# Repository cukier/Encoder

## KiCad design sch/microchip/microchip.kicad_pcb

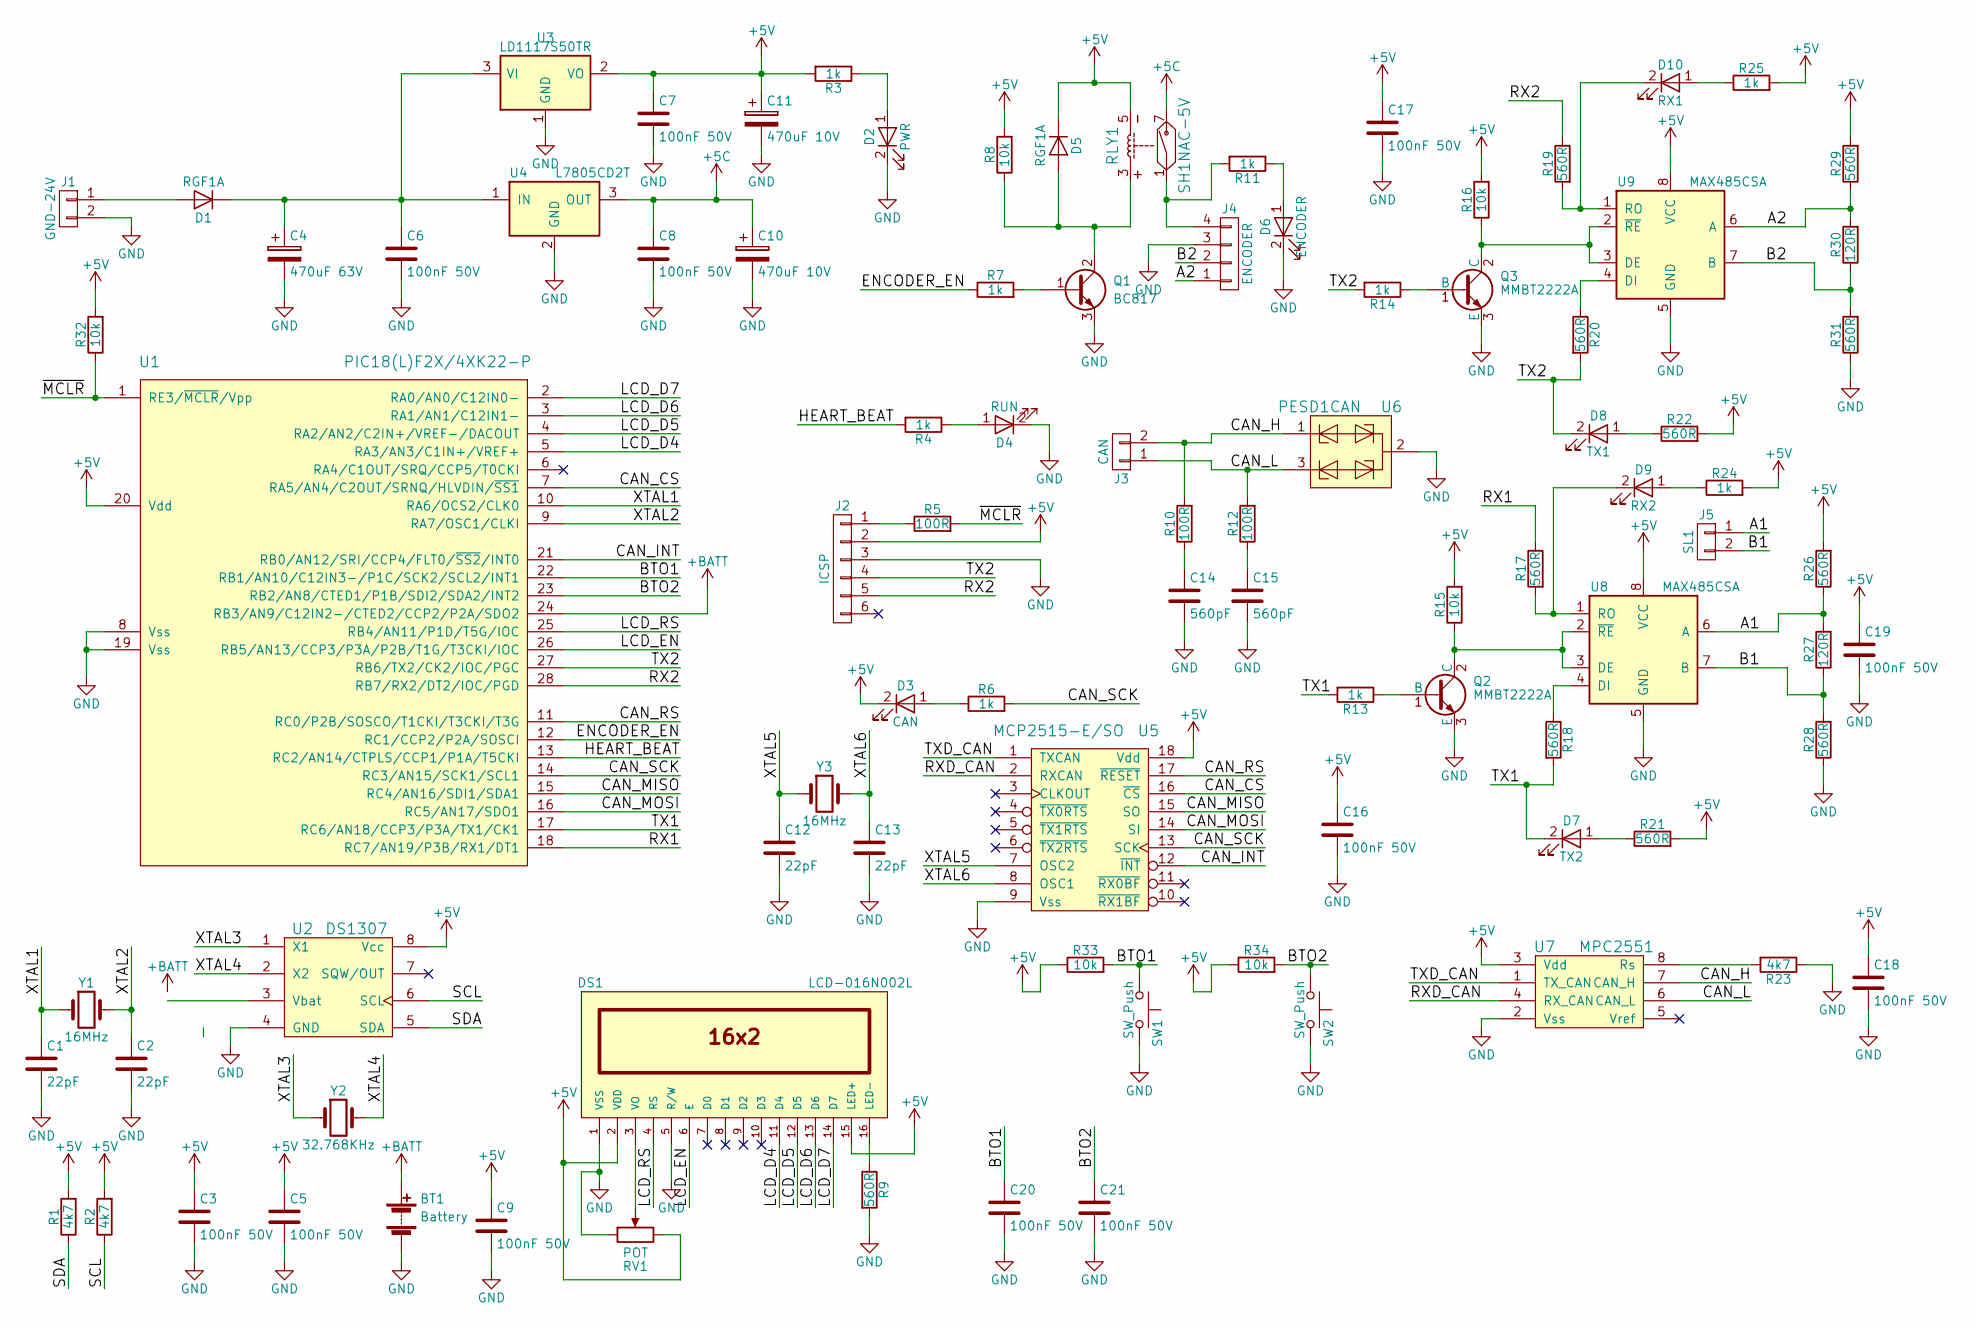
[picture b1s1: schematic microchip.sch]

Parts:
BT1: Battery; keystone_103
C1, C2, C12, C13: 22pF; c_0805
C3, C5, C6, C7, C8, C9, C16, C17, C18, C19, C20, C21: 100nF 50V; c_0805
C4: 470uF 63V; CP_12.5x25mm
C10, C11: 470uF 10V; CP_8x11.5mm
C14, C15: 560pF; c_0805
D1, D5: RGF1A; do214ac
D2: PWR; Led_0805
D3: CAN; Led_0805
D4: RUN; Led_0805
D6: ENCODER; Led_0805
D7: TX2; Led_0805
D8: TX1; Led_0805
D9: RX2; Led_0805
D10: RX1; Led_0805
DS1: LCD-016N002L; lcd_16x2
J1: GND-24V; mkds_1,5-2
J2: ICSP; pin_strip_6
J3: CAN; mkds_1,5-2
J4: ENCODER; mkds_1,5-4
J5: SL1; mkds_1,5-2
Q1: BC817; sot23
Q2, Q3: MMBT2222A; sot23
R1, R2, R23: 4k7; r_0805
R3, R4, R6, R7, R11, R13, R14, R24, R25: 1k; r_0805
R5, R10, R12: 100R; r_0805
R8, R15, R16, R32, R33, R34: 10k; r_0805
R9, R17, R18, R19, R20, R21, R22, R26, R28, R29, R31: 560R; r_0805
R27, R30: 120R; r_0805
RLY1: SH1NAC-5V; relay_9001
RV1: POT; trim_murata_pva2a
SW1, SW2: SW_Push; PCB_PUSH
U1: PIC18(L)F2X/4XK22-P; qfn-28
U2: DS1307; so-8
U3: LD1117S50TR; sot223
U4: L7805CD2T; d2-pak
U5: MCP2515-E/SO; soic-18
U6: PESD1CAN; sot23
U7: MPC2551; so-8
U8, U9: MAX485CSA; so-8
Y1, Y3: 16MHz; crystal_hc-49%2fsmd
Y2: 32.768KHz; crystal_tc-26_horiz

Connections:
+5C: C8.1, C10.1, RLY1.7, U4.3 (OUT)
+5V: C3.1, C5.1, C7.1, C9.1, C11.1, C16.1, C17.1, C18.1, C19.1, D3.2 (K), D5.2 (K), DS1.2 (VDD), DS1.15 (LED+), J2.2, R1.2, R2.2, R3.2, R8.2, R15.2, R16.2, R21.2, R22.2, R24.2, R25.2, R26.2, R29.2, R32.2, R33.1, R34.1, RLY1.5, RV1.3, U1.20 (Vdd), U2.8 (Vcc), U3.2 (VO), U5.18 (Vdd), U7.3 (Vdd), U8.8 (VCC), U9.8 (VCC)
+BATT: BT1.1 (+), U1.24 (RB3/AN9/C12IN2-/CTED2/CCP2/P2A/SDO2)
/A1: J5.1, R26.1, R27.2, U8.6 (A)
/A2: J4.1, R29.1, R30.2, U9.6 (A)
/B1: J5.2, R27.1, R28.2, U8.7 (B)
/B2: J4.2, R30.1, R31.2, U9.7 (B)
/BTO1: C20.1, R33.2, SW1.1, U1.22 (RB1/AN10/C12IN3-/P1C/SCK2/SCL2/INT1)
/BTO2: C21.1, R34.2, SW2.1, U1.23 (RB2/AN8/CTED1/P1B/SDI2/SDA2/INT2)
/CAN_CS: U1.7 (RA5/AN4/C2OUT/SRNQ/HLVDIN/~SS1), U5.16 (~CS)
/CAN_H: J3.2, R10.2, U6.1, U7.7 (CAN_H)
/CAN_INT: U1.21 (RB0/AN12/SRI/CCP4/FLT0/~SS2~/INT0), U5.12 (~INT)
/CAN_L: J3.1, R12.2, U6.3, U7.6 (CAN_L)
/CAN_MISO: U1.15 (RC4/AN16/SDI1/SDA1), U5.15 (SO)
/CAN_MOSI: U1.16 (RC5/AN17/SDO1), U5.14 (SI)
/CAN_RS: U1.11 (RC0/P2B/SOSCO/T1CKI/T3CKI/T3G), U5.17 (~RESET)
/CAN_SCK: R6.2, U1.14 (RC3/AN15/SCK1/SCL1), U5.13 (SCK)
/ENCODER_EN: R7.1, U1.12 (RC1/CCP2/P2A/SOSCI)
/HEART_BEAT: R4.2, U1.13 (RC2/AN14/CTPLS/CCP1/P1A/T5CKI)
/LCD_D4: DS1.11 (D4), U1.5 (RA3/AN3/C1IN+/VREF+)
/LCD_D5: DS1.12 (D5), U1.4 (RA2/AN2/C2IN+/VREF-/DACOUT)
/LCD_D6: DS1.13 (D6), U1.3 (RA1/AN1/C12IN1-)
/LCD_D7: DS1.14 (D7), U1.2 (RA0/AN0/C12IN0-)
/LCD_EN: DS1.6 (E), U1.26 (RB5/AN13/CCP3/P3A/P2B/T1G/T3CKI/IOC)
/LCD_RS: DS1.4 (RS), U1.25 (RB4/AN11/P1D/T5G/IOC)
/RX1: R17.1, U1.18 (RC7/AN19/P3B/RX1/DT1)
/RX2: J2.5, R19.1, U1.28 (RB7/RX2/DT2/IOC/PGD)
/RXD_CAN: U5.2 (RXCAN), U7.4 (RX_CAN)
/SCL: R2.1, U2.6 (SCL)
/SDA: R1.1, U2.5 (SDA)
/TX1: D7.2 (K), R13.2, R18.2, U1.17 (RC6/AN18/CCP3/P3A/TX1/CK1)
/TX2: D8.2 (K), J2.4, R14.2, R20.2, U1.27 (RB6/TX2/CK2/IOC/PGC)
/TXD_CAN: U5.1 (TXCAN), U7.1 (TX_CAN)
/XTAL1: C1.1, U1.10 (RA6/OCS2/CLK0), Y1.1
/XTAL2: C2.1, U1.9 (RA7/OSC1/CLKI), Y1.2
/XTAL3: U2.1 (X1), Y2.1
/XTAL4: U2.2 (X2), Y2.2
/XTAL5: C12.1, U5.7 (OSC2), Y3.1
/XTAL6: C13.1, U5.8 (OSC1), Y3.2
/~MCLR: R5.2, R32.1, U1.1 (RE3/~MCLR~/Vpp)
GND: BT1.2 (-), C1.2, C2.2, C3.2, C4.2, C5.2, C6.2, C7.2, C8.2, C9.2, C10.2, C11.2, C12.2, C13.2, C14.2, C15.2, C16.2, C17.2, C18.2, C19.2, C20.2, C21.2, D2.2 (K), D4.2 (K), D6.2 (K), DS1.1 (VSS), DS1.5 (R/W), J1.2, J2.3, J4.3, Q1.3 (E), Q2.3 (E), Q3.3 (E), R9.2, R23.1, R28.1, R31.1, RV1.1, SW1.2, SW2.2, U1.8 (Vss), U1.19 (Vss), U2.4 (GND), U3.1 (GND), U4.2 (GND), U5.9 (Vss), U6.2, U7.2 (Vss), U8.5 (GND), U9.5 (GND)
unnamed: C4.1, C6.1, D1.2 (K), U3.3 (VI), U4.1 (IN)
unnamed: C14.1, R10.1
unnamed: C15.1, R12.1
unnamed: D1.1 (A), J1.1
unnamed: D2.1 (A), R3.1
unnamed: D3.1 (A), R6.1
unnamed: D4.1 (A), R4.1
unnamed: D5.1 (A), Q1.2 (C), R8.1, RLY1.3
unnamed: D6.1 (A), R11.1
unnamed: D7.1 (A), R21.1
unnamed: D8.1 (A), R22.1
unnamed: D9.1 (A), R24.1
unnamed: D9.2 (K), R17.2, U8.1 (RO)
unnamed: D10.1 (A), R25.1
unnamed: D10.2 (K), R19.2, U9.1 (RO)
unnamed: DS1.3 (VO), RV1.2
unnamed: DS1.16 (LED-), R9.1
unnamed: J2.1, R5.1
unnamed: J4.4, R11.2, RLY1.1
unnamed: Q1.1 (B), R7.2
unnamed: Q2.1 (B), R13.1
unnamed: Q2.2 (C), R15.1, U8.2 (~RE~), U8.3 (DE)
unnamed: Q3.1 (B), R14.1
unnamed: Q3.2 (C), R16.1, U9.2 (~RE~), U9.3 (DE)
unnamed: R18.1, U8.4 (DI)
unnamed: R20.1, U9.4 (DI)
unnamed: R23.2, U7.8 (Rs)

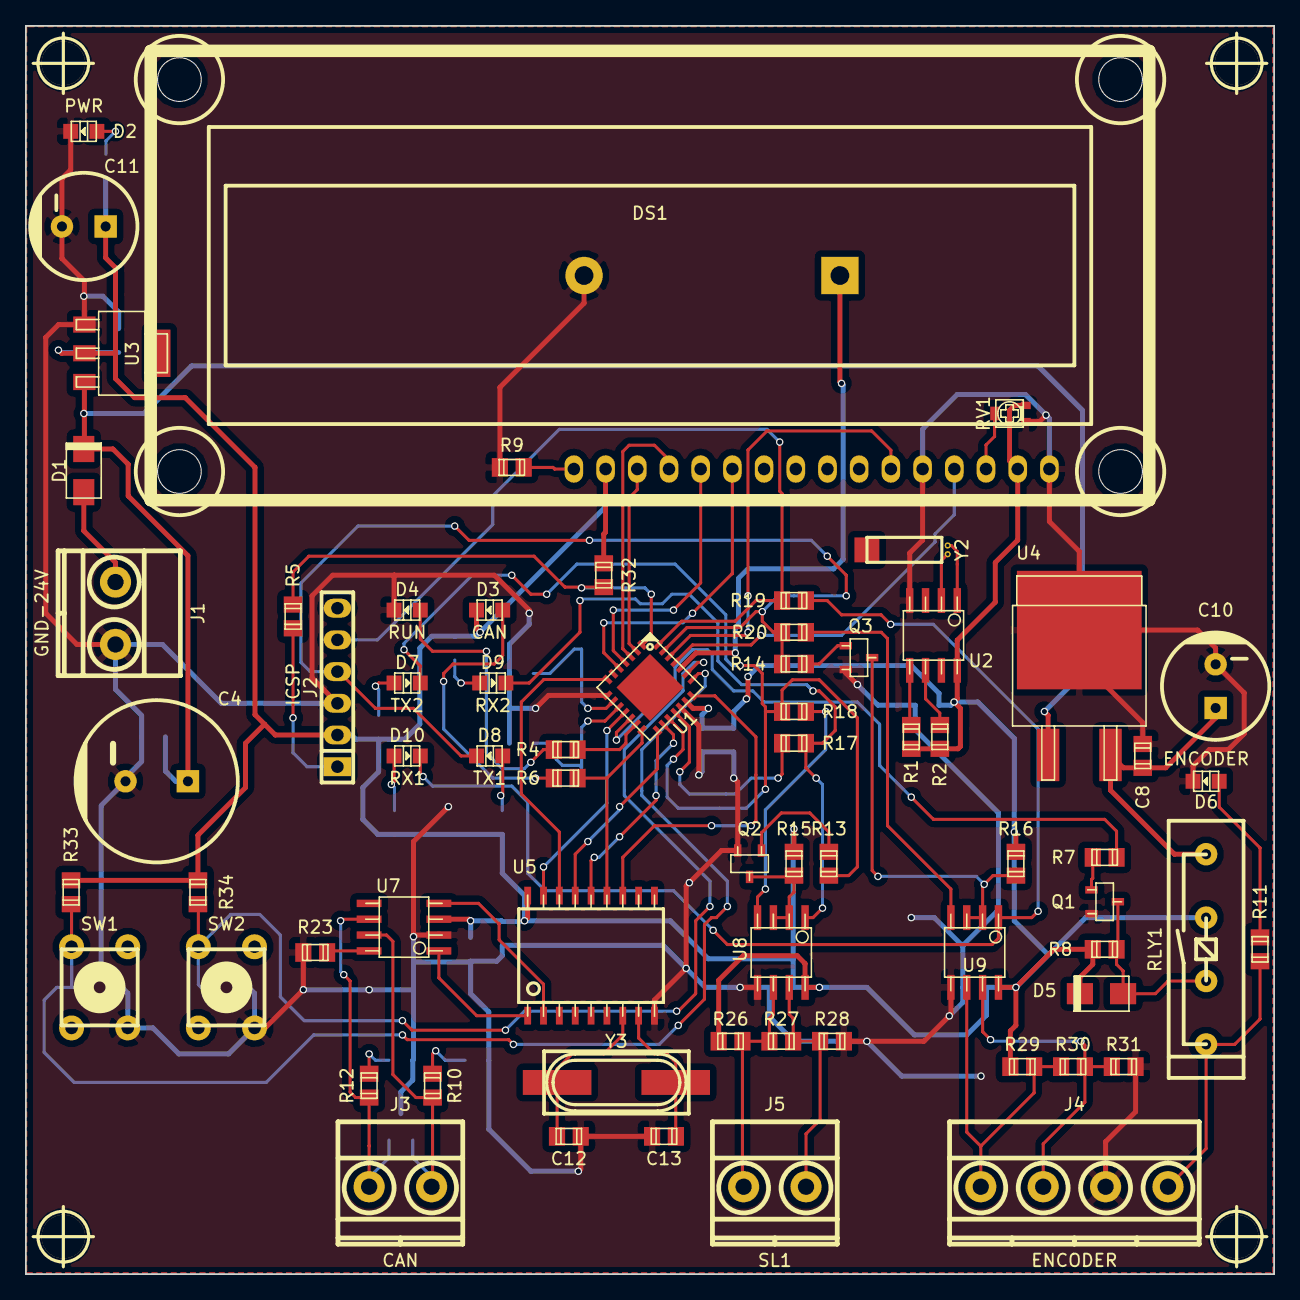
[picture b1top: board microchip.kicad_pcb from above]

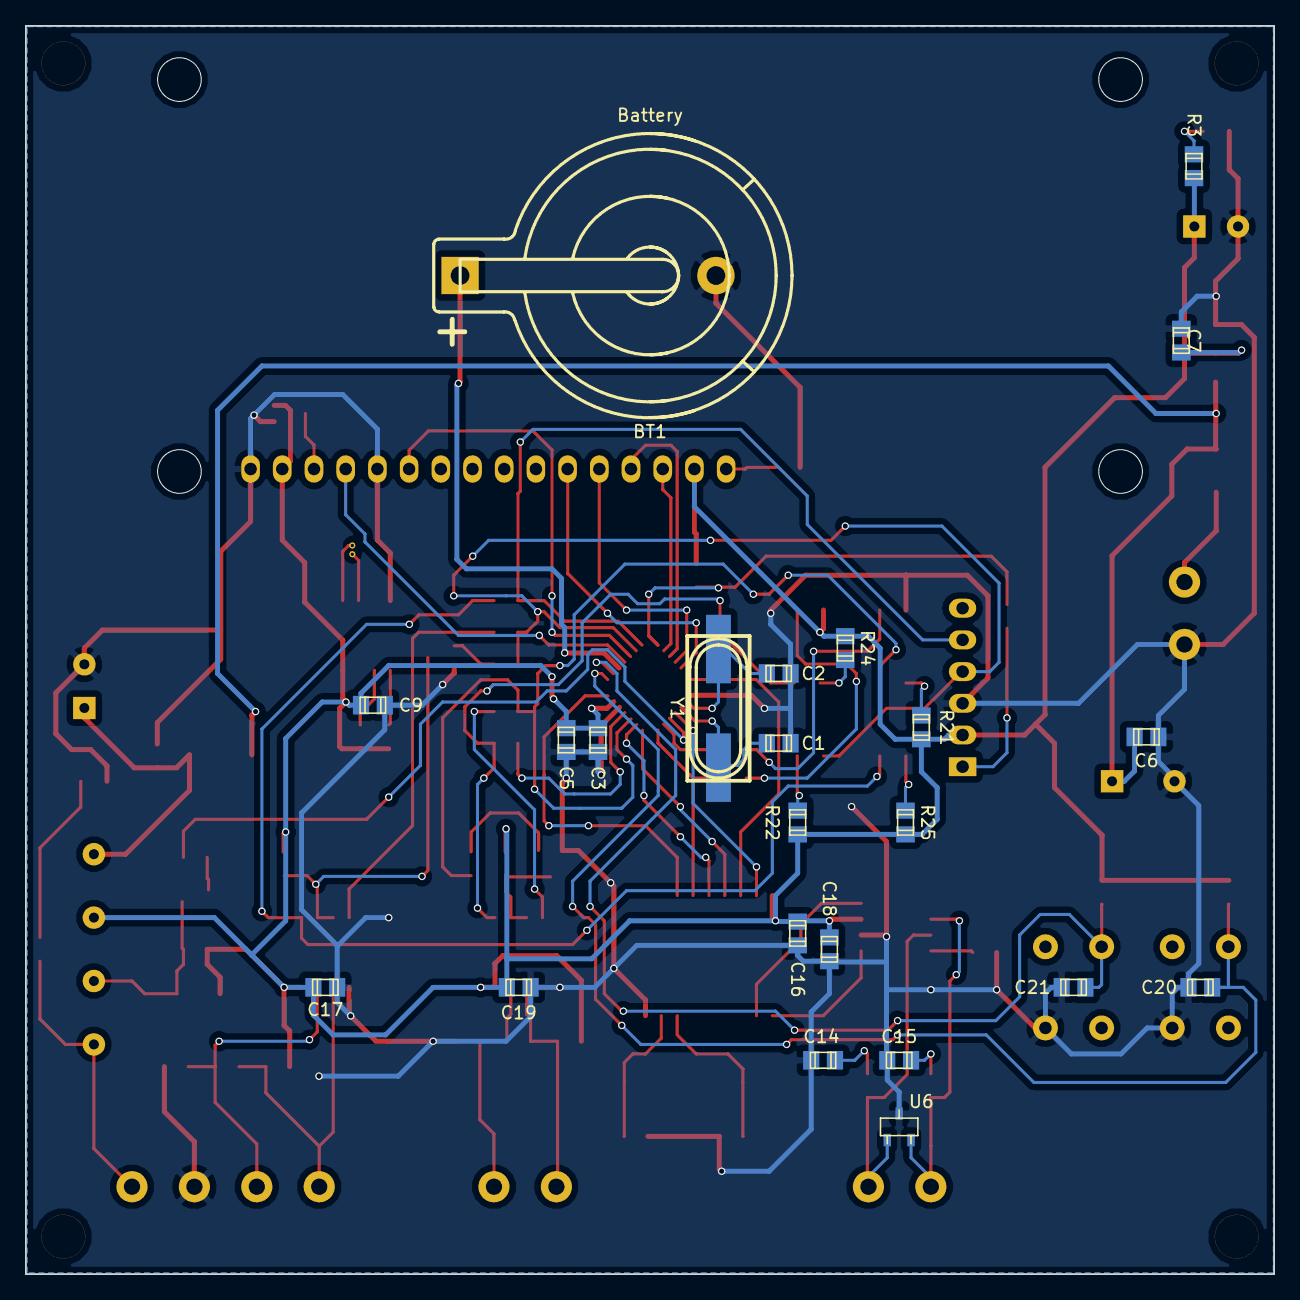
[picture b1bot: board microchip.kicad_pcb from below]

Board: 2 copper layers, 100.0 x 100.0 mm, 95 parts (23 on the bottom side), 68 nets.

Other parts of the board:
hole_3mm5, hole_3mm5#2, hole_3mm5#3, hole_3mm5#4: VAL**; hole_3mm5

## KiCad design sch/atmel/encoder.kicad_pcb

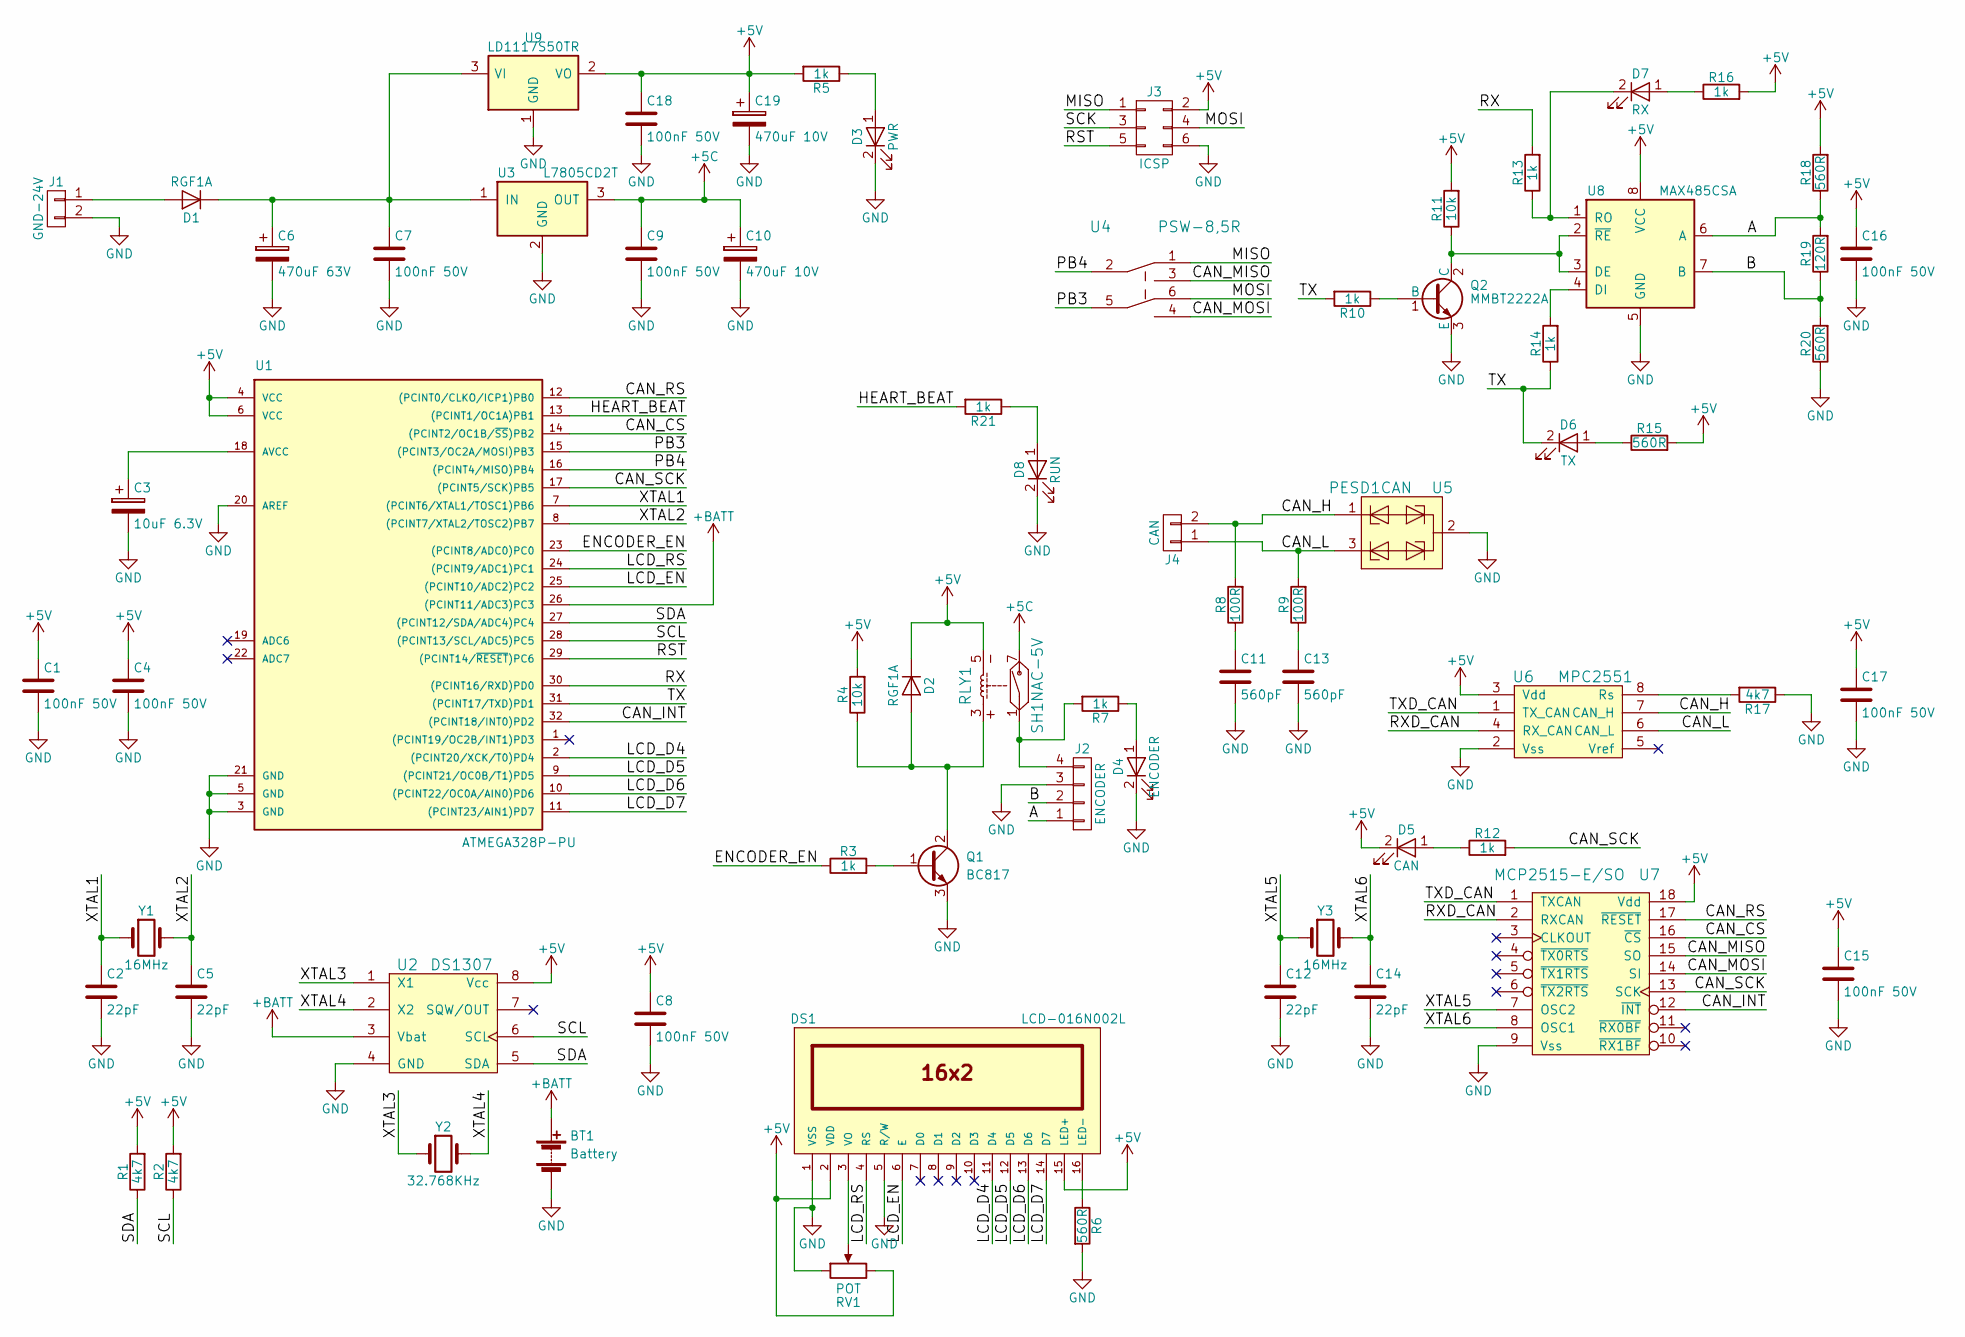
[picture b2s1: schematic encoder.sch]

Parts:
BT1: Battery; keystone_103
C1, C4, C7, C8, C9, C15, C16, C17, C18: 100nF 50V; c_0805
C2, C5, C12, C14: 22pF; c_0805
C3: 10uF 6.3V; CP_5x11mm
C6: 470uF 63V; CP_12.5x25mm
C10, C19: 470uF 10V; CP_8x11.5mm
C11, C13: 560pF; c_0805
D1, D2: RGF1A; do214ac
D3: PWR; Led_0805
D4: ENCODER; Led_0805
D5: CAN; Led_0805
D6: TX; Led_0805
D7: RX; Led_0805
D8: RUN; Led_0805
DS1: LCD-016N002L; lcd_16x2
J1: GND-24V; mkds_1,5-2
J2: ENCODER; mkds_1,5-4
J3: ICSP; pin_strip_3x2
J4: CAN; mkds_1,5-2
Q1: BC817; sot23
Q2: MMBT2222A; sot23
R1, R2, R17: 4k7; r_0805
R3, R5, R7, R10, R12, R13, R14, R16, R21: 1k; r_0805
R4, R11: 10k; r_0805
R6, R15, R18, R20: 560R; r_0805
R8, R9: 100R; r_0805
R19: 120R; r_0805
RLY1: SH1NAC-5V; relay_9001
RV1: POT; trim_murata_pva2a
U1: ATMEGA328P-PU; lqfp32
U2: DS1307; so-8
U3: L7805CD2T; d2-pak
U4: PSW-8,5R; psw-8,5
U5: PESD1CAN; sot23
U6: MPC2551; so-8
U7: MCP2515-E/SO; soic-18
U8: MAX485CSA; so-8
U9: LD1117S50TR; sot223
Y1, Y3: 16MHz; crystal_hc-49%2fsmd
Y2: 32.768KHz; crystal_tc-26_horiz

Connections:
+5C: C9.1, C10.1, RLY1.7, U3.3 (OUT)
+5V: C1.1, C4.1, C8.1, C15.1, C16.1, C17.1, C18.1, C19.1, D2.2 (K), D5.2 (K), DS1.2 (VDD), DS1.15 (LED+), J3.2, R1.2, R2.2, R4.2, R5.2, R11.2, R15.2, R16.2, R18.2, RLY1.5, RV1.3, U1.4 (VCC), U1.6 (VCC), U2.8 (Vcc), U6.3 (Vdd), U7.18 (Vdd), U8.8 (VCC), U9.2 (VO)
+BATT: BT1.1 (+), U1.26 ((PCINT11/ADC3)PC3), U2.3 (Vbat)
/A: J2.1, R18.1, R19.2, U8.6 (A)
/B: J2.2, R19.1, R20.2, U8.7 (B)
/CAN_CS: U1.14 ((PCINT2/OC1B/~SS~)PB2), U7.16 (~CS)
/CAN_H: J4.2, R8.2, U5.1, U6.7 (CAN_H)
/CAN_INT: U1.32 ((PCINT18/INT0)PD2), U7.12 (~INT)
/CAN_L: J4.1, R9.2, U5.3, U6.6 (CAN_L)
/CAN_MISO: U4.3, U7.15 (SO)
/CAN_MOSI: U4.4, U7.14 (SI)
/CAN_RS: U1.12 ((PCINT0/CLKO/ICP1)PB0), U7.17 (~RESET)
/CAN_SCK: R12.2, U1.17 ((PCINT5/SCK)PB5), U7.13 (SCK)
/ENCODER_EN: R3.1, U1.23 ((PCINT8/ADC0)PC0)
/HEART_BEAT: R21.2, U1.13 ((PCINT1/OC1A)PB1)
/LCD_D4: DS1.11 (D4), U1.2 ((PCINT20/XCK/T0)PD4)
/LCD_D5: DS1.12 (D5), U1.9 ((PCINT21/OC0B/T1)PD5)
/LCD_D6: DS1.13 (D6), U1.10 ((PCINT22/OC0A/AIN0)PD6)
/LCD_D7: DS1.14 (D7), U1.11 ((PCINT23/AIN1)PD7)
/LCD_EN: DS1.6 (E), U1.25 ((PCINT10/ADC2)PC2)
/LCD_RS: DS1.4 (RS), U1.24 ((PCINT9/ADC1)PC1)
/MISO: J3.1, U4.1
/MOSI: J3.4, U4.6
/PB3: U1.15 ((PCINT3/OC2A/MOSI)PB3), U4.5
/PB4: U1.16 ((PCINT4/MISO)PB4), U4.2
/RST: J3.5, U1.29 ((PCINT14/~RESET~)PC6)
/RX: R13.2, U1.30 ((PCINT16/RXD)PD0)
/RXD_CAN: U6.4 (RX_CAN), U7.2 (RXCAN)
/SCK: J3.3
/SCL: R2.1, U1.28 ((PCINT13/SCL/ADC5)PC5), U2.6 (SCL)
/SDA: R1.1, U1.27 ((PCINT12/SDA/ADC4)PC4), U2.5 (SDA)
/TX: D6.2 (K), R10.2, R14.1, U1.31 ((PCINT17/TXD)PD1)
/TXD_CAN: U6.1 (TX_CAN), U7.1 (TXCAN)
/XTAL1: C2.1, U1.7 ((PCINT6/XTAL1/TOSC1)PB6), Y1.1
/XTAL2: C5.1, U1.8 ((PCINT7/XTAL2/TOSC2)PB7), Y1.2
/XTAL3: U2.1 (X1), Y2.1
/XTAL4: U2.2 (X2), Y2.2
/XTAL5: C12.1, U7.7 (OSC2), Y3.1
/XTAL6: C14.1, U7.8 (OSC1), Y3.2
GND: BT1.2 (-), C1.2, C2.2, C3.2, C4.2, C5.2, C6.2, C7.2, C8.2, C9.2, C10.2, C11.2, C12.2, C13.2, C14.2, C15.2, C16.2, C17.2, C18.2, C19.2, D3.2 (K), D4.2 (K), D8.2 (K), DS1.1 (VSS), DS1.5 (R/W), J1.2, J2.3, J3.6, Q1.3 (E), Q2.3 (E), R6.2, R17.1, R20.1, RV1.1, U1.3 (GND), U1.5 (GND), U1.20 (AREF), U1.21 (GND), U2.4 (GND), U3.2 (GND), U5.2, U6.2 (Vss), U7.9 (Vss), U8.5 (GND), U9.1 (GND)
unnamed: C3.1, U1.18 (AVCC)
unnamed: C6.1, C7.1, D1.2 (K), U3.1 (IN), U9.3 (VI)
unnamed: C11.1, R8.1
unnamed: C13.1, R9.1
unnamed: D1.1 (A), J1.1
unnamed: D2.1 (A), Q1.2 (C), R4.1, RLY1.3
unnamed: D3.1 (A), R5.1
unnamed: D4.1 (A), R7.1
unnamed: D5.1 (A), R12.1
unnamed: D6.1 (A), R15.1
unnamed: D7.1 (A), R16.1
unnamed: D7.2 (K), R13.1, U8.1 (RO)
unnamed: D8.1 (A), R21.1
unnamed: DS1.3 (VO), RV1.2
unnamed: DS1.16 (LED-), R6.1
unnamed: J2.4, R7.2, RLY1.1
unnamed: Q1.1 (B), R3.2
unnamed: Q2.1 (B), R10.1
unnamed: Q2.2 (C), R11.1, U8.2 (~RE~), U8.3 (DE)
unnamed: R14.2, U8.4 (DI)
unnamed: R17.2, U6.8 (Rs)

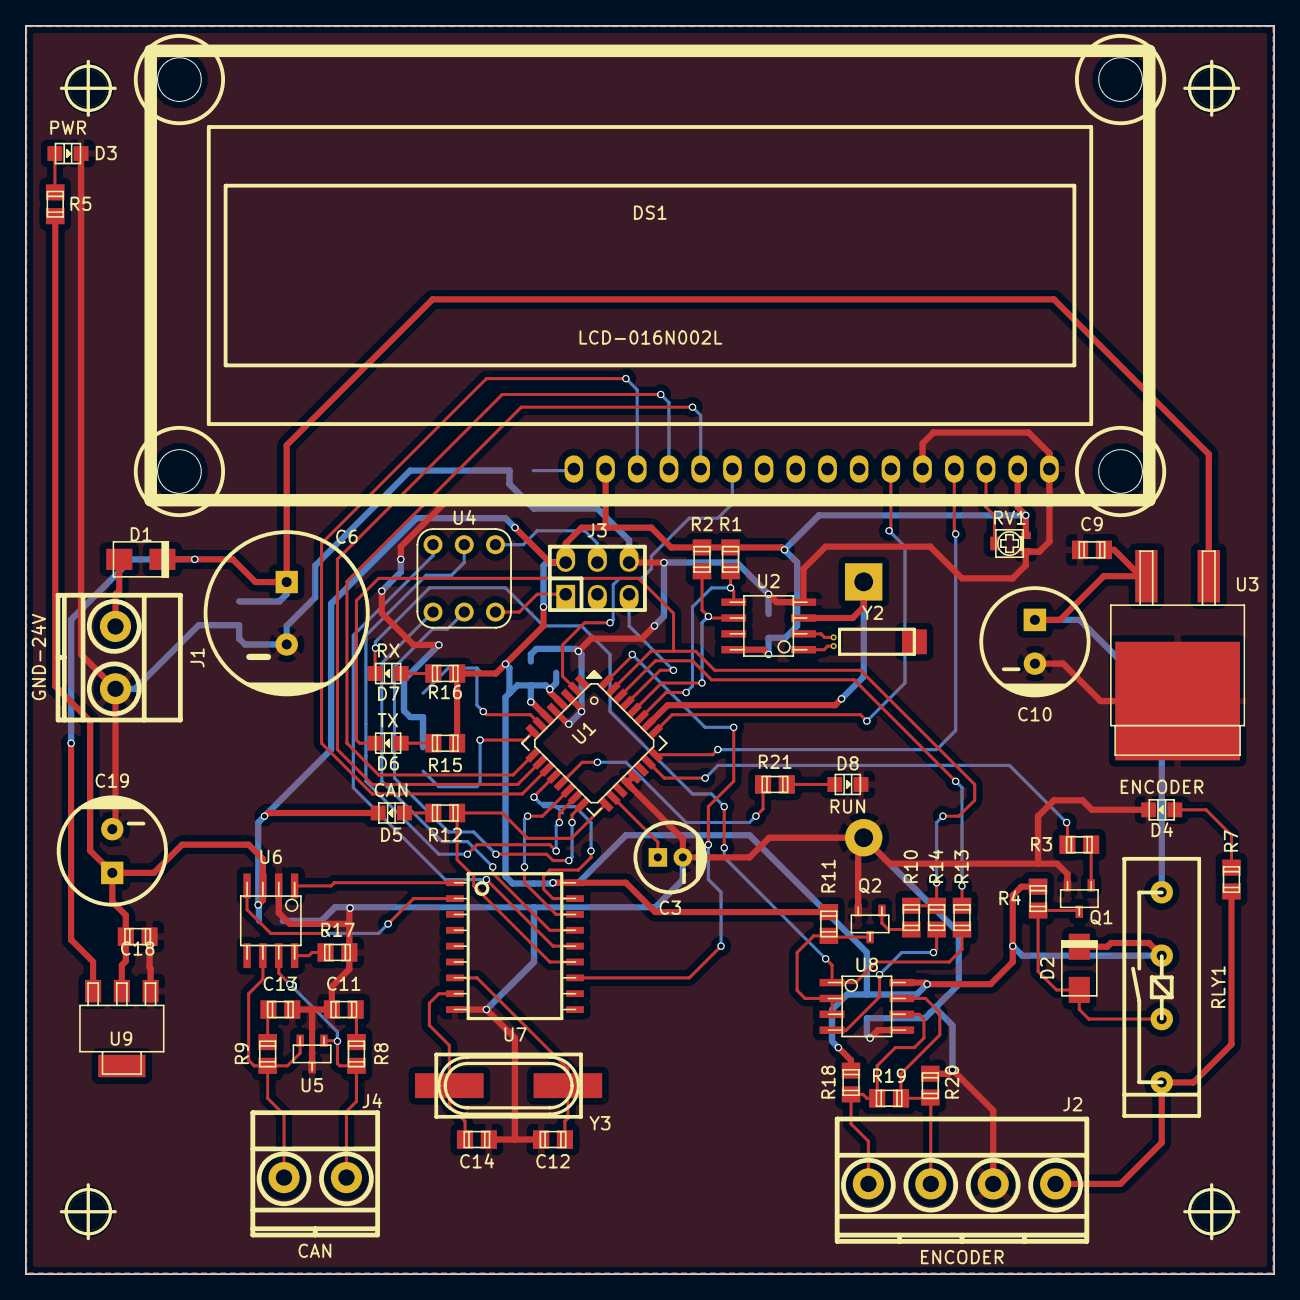
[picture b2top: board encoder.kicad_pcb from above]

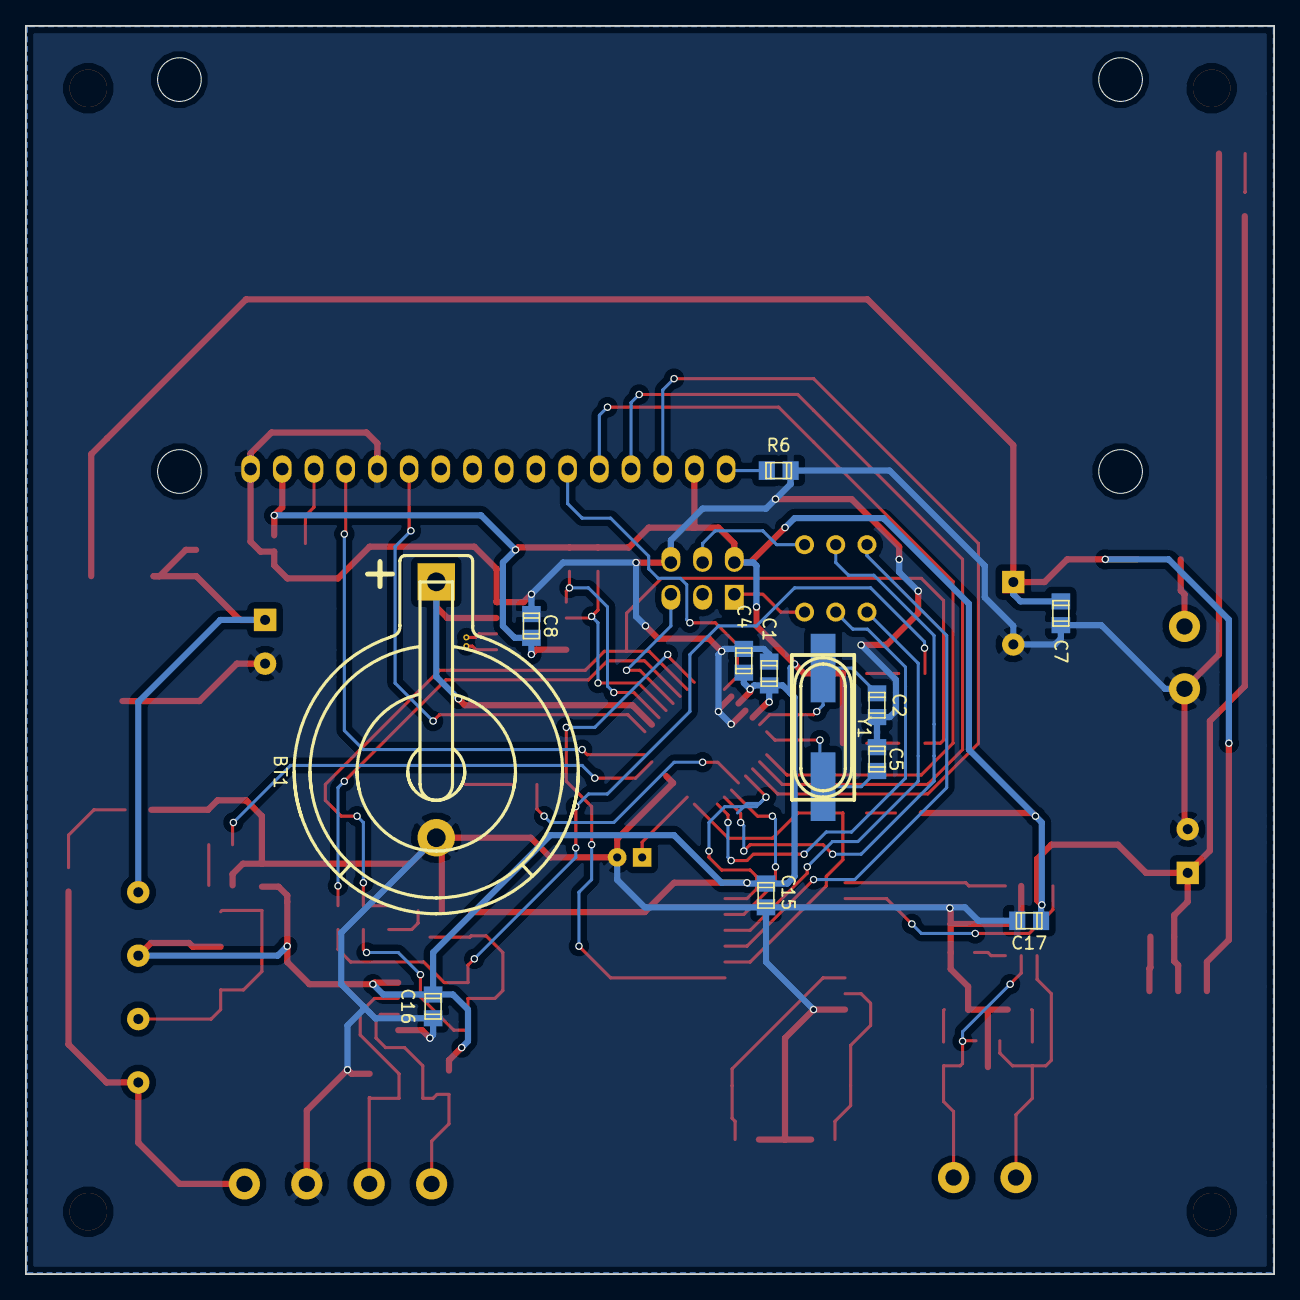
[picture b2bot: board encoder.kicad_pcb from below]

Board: 2 copper layers, 100.0 x 100.0 mm, 74 parts (12 on the bottom side), 60 nets.

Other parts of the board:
hole_3mm, hole_3mm#2, hole_3mm#3, hole_3mm#4: VAL**; hole_3mm

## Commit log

2013-01-07 primeiro
2013-01-07 funcionando para encoder AS4050
2013-01-07 afsd
2013-01-08 funcionado encoder em SPI programamdno timer 0
2013-01-15 teste timer
2013-01-16 funcionando contagem por quadratura encoder AM8192B e AM4096
2013-01-17 altercao para i2c
2013-01-17 alteracao i2c 2
2013-03-04 Fechando RENISHAW
2013-03-15 Adicionada sch encoder
2013-03-15 atualizacao
2013-03-19 alterando para 18F45K20
2013-03-22 4050AZ
2013-03-22 clear_bus
2013-03-22 asdf
2013-03-23 teste para programacao tipo soft as5040 (datasheet ou AN5000-20)
2013-03-23 teste
2013-03-23 tempos para prog corrigidos
2013-03-23 arrumando tempos prog e comunic
2013-03-23 aparentemente funcionando programcao soft
2013-03-23 adicionando modulo ccp para uso do modo AB
2013-03-25 tsete
2013-03-27 limpando RAM
2013-03-27 construcao simulador coluna
2013-03-27 elevador sim em andamento
2013-03-27 elevador sim em construcao
2013-03-28 AS5040 AZ pronto
2013-07-31 fafsda
2013-07-31 continuando
2013-07-31 funcionando para leitura do AD4050 apenas
2013-07-31 gfkh
2013-08-01 testes
2013-08-01 contagem 1
2013-08-01 testando sentido
2013-08-02 inicio testes encoder + comunicacao i2c
2013-08-02 teste de comunicacao + encoder continua no projeto do elevador....
2013-08-02 ultimo commit
2014-02-13 teste ternario
2014-02-14 testando placa
2014-02-17 teste de botoes ok
2014-02-24 botoes ok
2014-02-25 teste de vida de variavel
2014-02-26 quadratura usando timer1
2014-08-25 lendo a diferenca de movimento e sentido usando os canais a e b como clocks dos timers 0 e 1
2014-08-26 todo: leitura de encoder de quadratura usando ext ints.
2014-08-26 feito com interrupcao
2014-08-26 lendo encoder de quadratura e direcao usando interrupcao de mudanca no port_b
2014-10-27 decoder para encoder sick DFS60
2014-11-03 bug fix: filtragem da interrupcao
2017-06-28 esquematico encoder CAN
2017-06-28 blink atmel ok avr-gcc -D__AVR_ATmega328P__ -Os -g3 -Wall -c -fmessage-length=0 -mmcu=atmega328p -MMD -MP -MF"src/main.d" -MT"src/main.o" -o "src/main.o" "../src/main.c"
2017-06-29 modbus
2017-07-03 placa endcoder
2017-07-04 sim sick.c sick.h
2017-07-04 lcd e heart_beat
2017-07-04 lende posicao e mostrando lcd
2017-07-04 regulador tensao d2pak
2017-07-06 library can
2017-07-06 correcao rele alimentacao encoder
2017-07-06 nova bibliotaca uart
2017-07-06 nova biblioteca uart
2017-07-10 encoder serial
2017-07-11 heart beat Signed-off-by: cuki2 <mauricio@krebs.com.br>
2017-07-11 endereco do angulo
2017-07-12 resolucao
2017-07-12 resolucao ok
2017-07-14 rtos ex
2017-07-14 rtos
2017-07-24 placa microchip
